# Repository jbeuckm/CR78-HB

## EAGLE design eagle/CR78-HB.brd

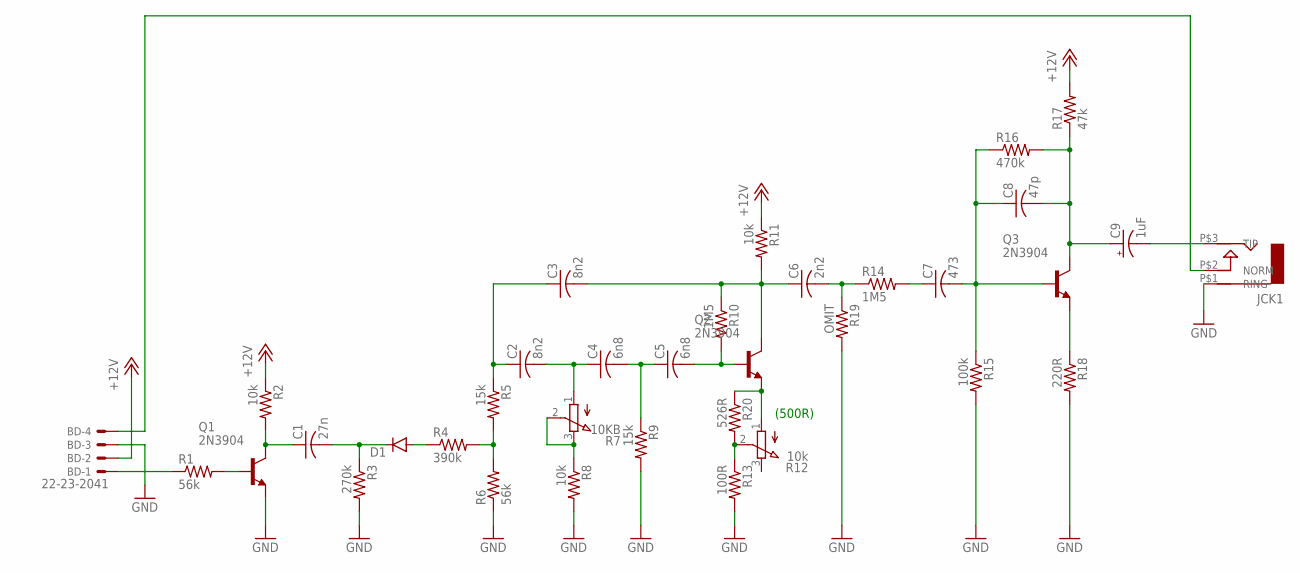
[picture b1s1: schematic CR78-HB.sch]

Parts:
BD: 22-23-2041
C1: 27n; C050-025X075
C2, C3: 8n2; C050-025X075
C4, C5: 6n8; C050-025X075
C6: 2n2; C050-025X075
C7: 473; C050-025X075
C8: 47p; C050-025X075
C9: 1uF; B45181A
D1: DIODE1N4148; DIODE-1N4148
JCK1: AUDIO-JACK; ERTHENVAR-JACK-90DEG
Q1, Q2, Q3: 2N3904; TO92
R1, R6: 56k; 0207/7
R2, R8, R11: 10k; 0207/7
R3: 270k; 0207/7
R4: 390k; 0207/7
R5: 15k; 0207/7
R7: 10KB; 3RP/1610N
R9: 15k; 0207/5V
R10, R14: 1M5; 0207/7
R12: 10k; 3RP/1610N
R13: 100R; 0207/7
R15: 100k; 0207/7
R16: 470k; 0207/7
R17: 47k; 0207/7
R18: 220R; 0207/7
R19: OMIT; 0207/5V
R20: 526R; 0207/5V

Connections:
+12V: BD.2, R2.1, R11.1, R17.2
GND: BD.3, JCK1.P$1 (RING), Q1.3 (E), R3.2, R6.1, R8.2, R9.2, R13.2, R15.2, R18.2, R19.2
unnamed: C1.2, D1.C, R3.1
unnamed: D1.A, R4.1
unnamed: R4.2, R5.2, R6.2
unnamed: C2.1, C3.1, R5.1
unnamed: R7.2 (S), R7.3 (E), R8.1
unnamed: C2.2, C4.1, R7.1 (A)
unnamed: C5.2, Q2.2 (B), R10.2
unnamed: R12.2 (S), R13.1, R20.2
unnamed: C3.2, C6.1, Q2.1 (C), R10.1, R11.2
unnamed: C4.2, C5.1, R9.1
unnamed: BD.1, R1.1
unnamed: BD.4, JCK1.P$2 (NORM)
unnamed: Q2.3 (E), R12.1 (A), R20.1
unnamed: C6.2, R14.1, R19.1
unnamed: Q3.3 (E), R18.1
unnamed: C8.2, C9.+, Q3.1 (C), R16.2, R17.1
unnamed: C7.1, R14.2
unnamed: C7.2, C8.1, Q3.2 (B), R15.1, R16.1
unnamed: C9.-, JCK1.P$3 (TIP)
unnamed: C1.1, Q1.1 (C), R2.2
unnamed: Q1.2 (B), R1.2

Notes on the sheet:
(500R)

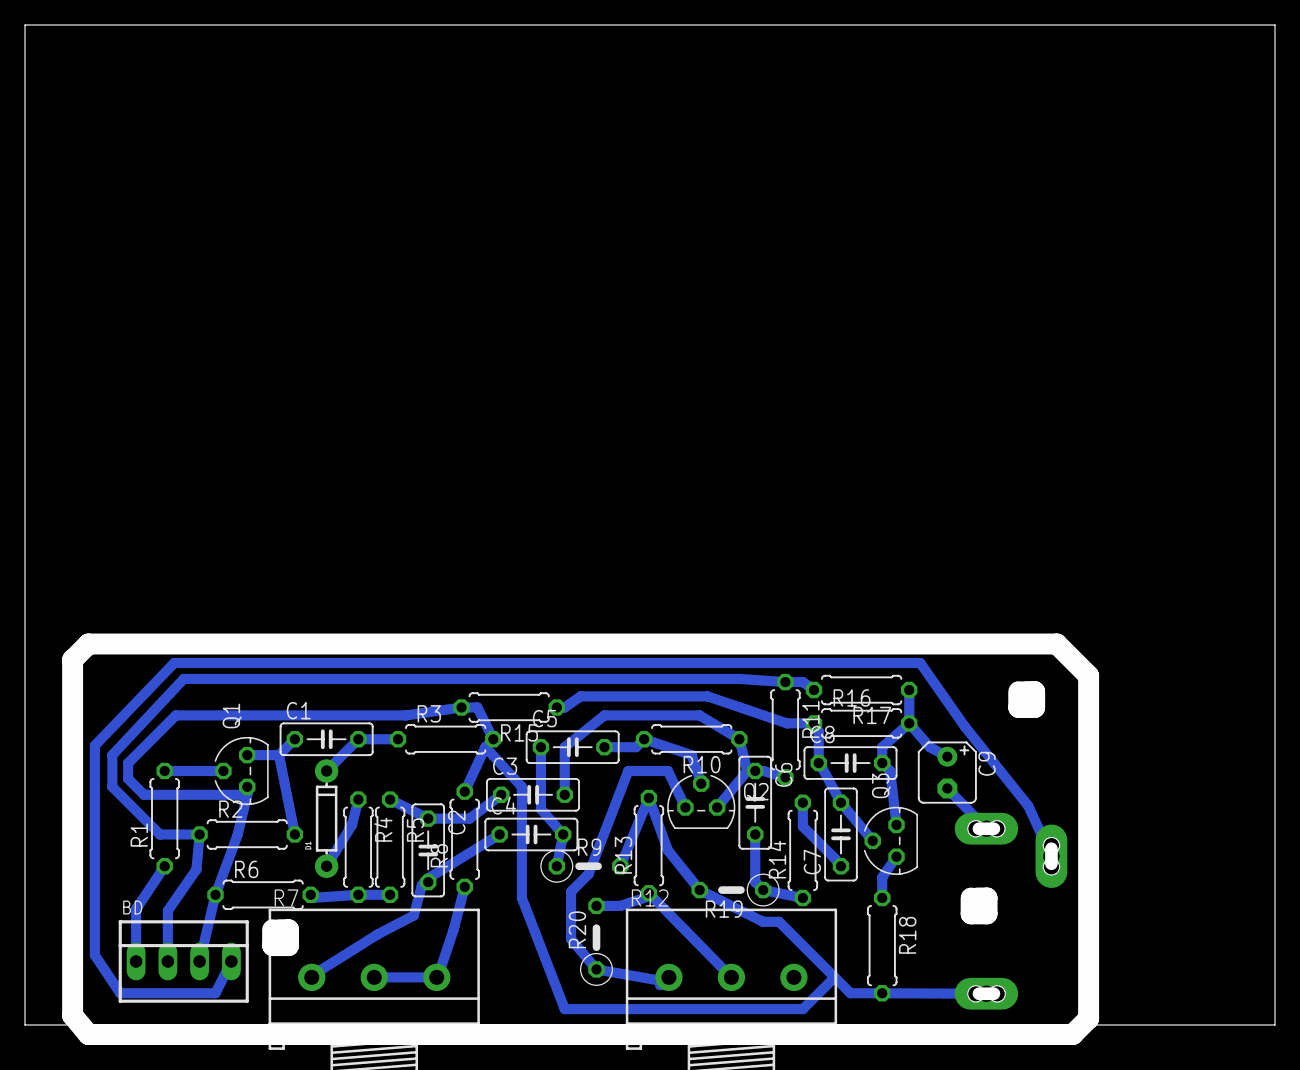
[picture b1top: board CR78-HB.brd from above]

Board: 2 copper layers, 98.3 x 79.9 mm, 35 parts (0 on the bottom side), 23 nets.

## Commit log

2016-05-31 minimized routing
2016-05-31 cutout
2016-06-01 gcode
2016-06-01 added output pulldown 10k for bd
2016-06-08 routed with panel pots
2016-06-08 tweaks
2016-06-08 routed with pot change resistor value
2016-06-11 values for LC
2016-06-11 values for LB
2016-06-11 values for HB
2016-10-22 working up panel for bd lb hb hc
2016-10-22 panel dxf
2016-10-22 stroke to path dxf
2016-10-22 spline checkbox
2016-10-22 no lwpoly output
2016-10-22 no checkbox mm output
2016-10-22 unlink clone
2016-10-22 object to path

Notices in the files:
parts and their libraries:
SparkFun-DiscreteSemi: Licensing: Creative Commons ShareAlike 4.0 International - https://creativecommons.org/licenses/by-sa/4.0
